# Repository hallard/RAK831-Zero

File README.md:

# Raspberry PI Zero RAK831 Lora Gateway Shield

This shield has been created to help wiring between Raspberry PI Zero and [RAK831][10] LoraWan concentrator Gateway and to be able to put the whole thing into a enclosure..

Then I decided to add some funky stuff like:

## Features (tested, working fine)

**Major updates in V1.5a**

 - Added connector to put a [Tiny GPS][46] breakout board 
 - Added switch/jumpers to select PI Serial to be connected to FTDI connector or from GPS RX/TX
 - Added footprint for RTC components or [Adafruit Breakout][47] (when used in local LoRaWAN server without Internet connexion)
 - Added a LED on ~~GPIO4~~ GPIO26 to light when GW is off so we can remove power safely (or whatever purpose)
 - Connected GPS PPS signal on GPIO4 and added a LED on this signal
 - **due to space constraints because of new features, some options to put PTH components have been removed**

**Minor tweaks in V1.4**

 - Labeling error on top silk for Murata OKI-78SR-5 (VIN VOUT were revesed) but correct on bottom silk
 - Added solder bat to be able to reverse 3V3/GND and/or SCL/SDA on I2C-1 connector 
 - Moved FTDI connector to lower position
 - Added I2C connector SILK number to identify them better
 - Added a LED on GPIO4 to light when GW is off so we can remove power safely

**Minor tweaks in V1.3b**

 - Reversed side of Murata OKI-78SR-5 to let some place for big OLED
 - Changed solder pad default power to use DC/DC 
 - Inversed the 2 OLED connectors to better seeing of RAK LED
 - Adjusted opening to see RAK LED to a better position

**Since V1.3**

 - Push button on GPIO17 to be able to shutdown PI Locally
 - Added FTDI connector to be able to take hand on PI console when in enclosure (lost network or whatever, no more need to get all off the enclosure and connect HDMI cable to see what's going on)
 - Added footprint for excellent Murata OKI-78SR-5 DC/DC 5V
 - Footprint for [RAK831][10] LoraWan concentrator (main goal)
 - I2C connectors to be able to add internal/external sensors or OLED such as BME280, SI7021, HTU21D SSD1306
 - Power with terminal block
 - 2 visual WS2812B Leds
 - Easy to build and solder, 0805 or PTH components
 - Holes to fix board on enclosure or other support
 - quick fix connector, you can plug/unplug PI Zero without soldering

Tiny GPS breakout board, buy [there][46]   

Tiny Adafruit RTC board, buy [there][47]    

## Detailed Description

No specific documentation for now, it's just a kind of wiring helper, please see Gateway section on [TTN Learn](https://www.thethingsnetwork.org/docs/gateways/) and also on [TTN Forums](https://www.thethingsnetwork.org/forum/t/the-hard-rak831-cafe-part-2/10576/) for more information on these gateways.

### Power

You can power the board with 5V going to Raspberry PI USB power directly or connecting 5V to the terminal blocks named VIN/GND, in this case use a descent 5V power supply. 

You can also use a Murata DC/DC Step down (see BOM), in this case you can power the board from DC 7V to 36V, this is what I do each time. ~~To use this feature you need to cut the trace on bottom side of PCB that connect VIN to 5V (vout)~~.

**Since V1.3b+ the trace is not connected anymore**. This means that Vin and Vout are not connected anymore. So if you don't use DC/DC and powering with 5V, you need to put some solder on the pad to connect vout to vin (5V).

### Pushbutton

The push button is connected between 3V3 and GPIO17. GPIO17 has a 10K pull down to ground so when pressed GPIO17 become High. The button can be soldered on board, or connected to the Terminal Blocks if you want to put an external one if you have the board in a closed enclosure for example.

Push button management is done my the monitoring service installed by the setup below

### LEDs

Led management is done my the monitoring service installed by the setup below

## Software Installation

Please follow the installation documented on the dedicated [repository][5] to install all needed and functionnal software:

- Initial configuration
- Multi Protocol Packet Forwarder
- Monitoring service (Led and Push Button)

## Schematics

## Boards 

### PCB 

**Top side**

**Bottom side**

### Assembled PCB (V1.3)

**Top side**

**Bottom side**

You can order the PCB of this board at PCBs.io 

- [V1.3][3] (obsolete)
- [V1.3b][4] (obsolete)
- [V1.4][6] 
- [V1.5a][8] Lastest one

Please not that there is special PCB version (not released yet) that fit in an indoor enclosure like the ones you can find on ebay. Search on ebay for `100x68x50mm IP66 Waterproof` or `100x68x50mm IP66 Waterproof clear` to find them.
- [V1.3][7] For outdoor enclosure (smaller PCB)

PCBs.io give me some reward when you order my designed boards from their site. This is pretty good, because I can use these rewards to create and design new boards and order boards for a discounted price, so if you don't care about PCB manufacturer please use PCBs.io.

## Assembled boards into nice enclosure 

With the samtec connector you can put the PI Zero on top or bottom, depending on your choice, just solder the sametec connector to the PCB side you need. You can also avoid connector soldering the PI directly on the board.

And here it is near to [The things node](https://www.thethingsnetwork.org/docs/devices/node/).

## Video of all

Click on image to see the video

## Bill Of Material

Nothing fancy, all components are 0805 and/or PTH and can be ordered almost anywhere (digikey, mouser, radiospare, ...). 
use only what you need dependings on what you want to do. You can find lot of components on ebay or aliexpress, but since vendors are often ephemere, I put for reference the BOM on well known providers.

Here is the [octopart BOM](https://octopart.com/bom-tool/bSeZiAE7)

If you have good reference for standoff like [this][44], just let me know.

## License

This work is licensed under a [Creative Commons Attribution-NonCommercial 4.0 International License](http://creativecommons.org/licenses/by-nc/4.0/)    
If you want to do commercial stuff with this project, please contact [CH2i company](https://www.ch2i.eu/en#support) so we can organize an simple agreement.

# Misc

See news and other projects on my [blog][1] 
 
[1]: https://hallard.me
[3]: https://PCBs.io/share/rpqDd
[4]: https://PCBs.io/share/z722g
[6]: https://PCBs.io/share/4qKoO
[7]: https://PCBs.io/share/zvYLj
[8]: https://www.pcbs.io/share/rwjd1

[5]: https://github.com/ch2i/LoraGW-Setup
[10]: http://www.rakwireless.com/en/WisKeyOSH/RAK831
[44]: https://www.ebay.com/itm/162036913864?var=461005633671
[45]: http://www2.mouser.com/ProductDetail/Murata-Power-Solutions/OKI-78SR-5-15-W36H-C/?qs=sGAEpiMZZMt6Q9lZSPl3Rb6uckMsyldgZf%2f4GdkUxM8%3d
[46]: http://www.electrodragon.com/product/gnss-module-atgm336h/
[47]: https://www.adafruit.com/product/3295

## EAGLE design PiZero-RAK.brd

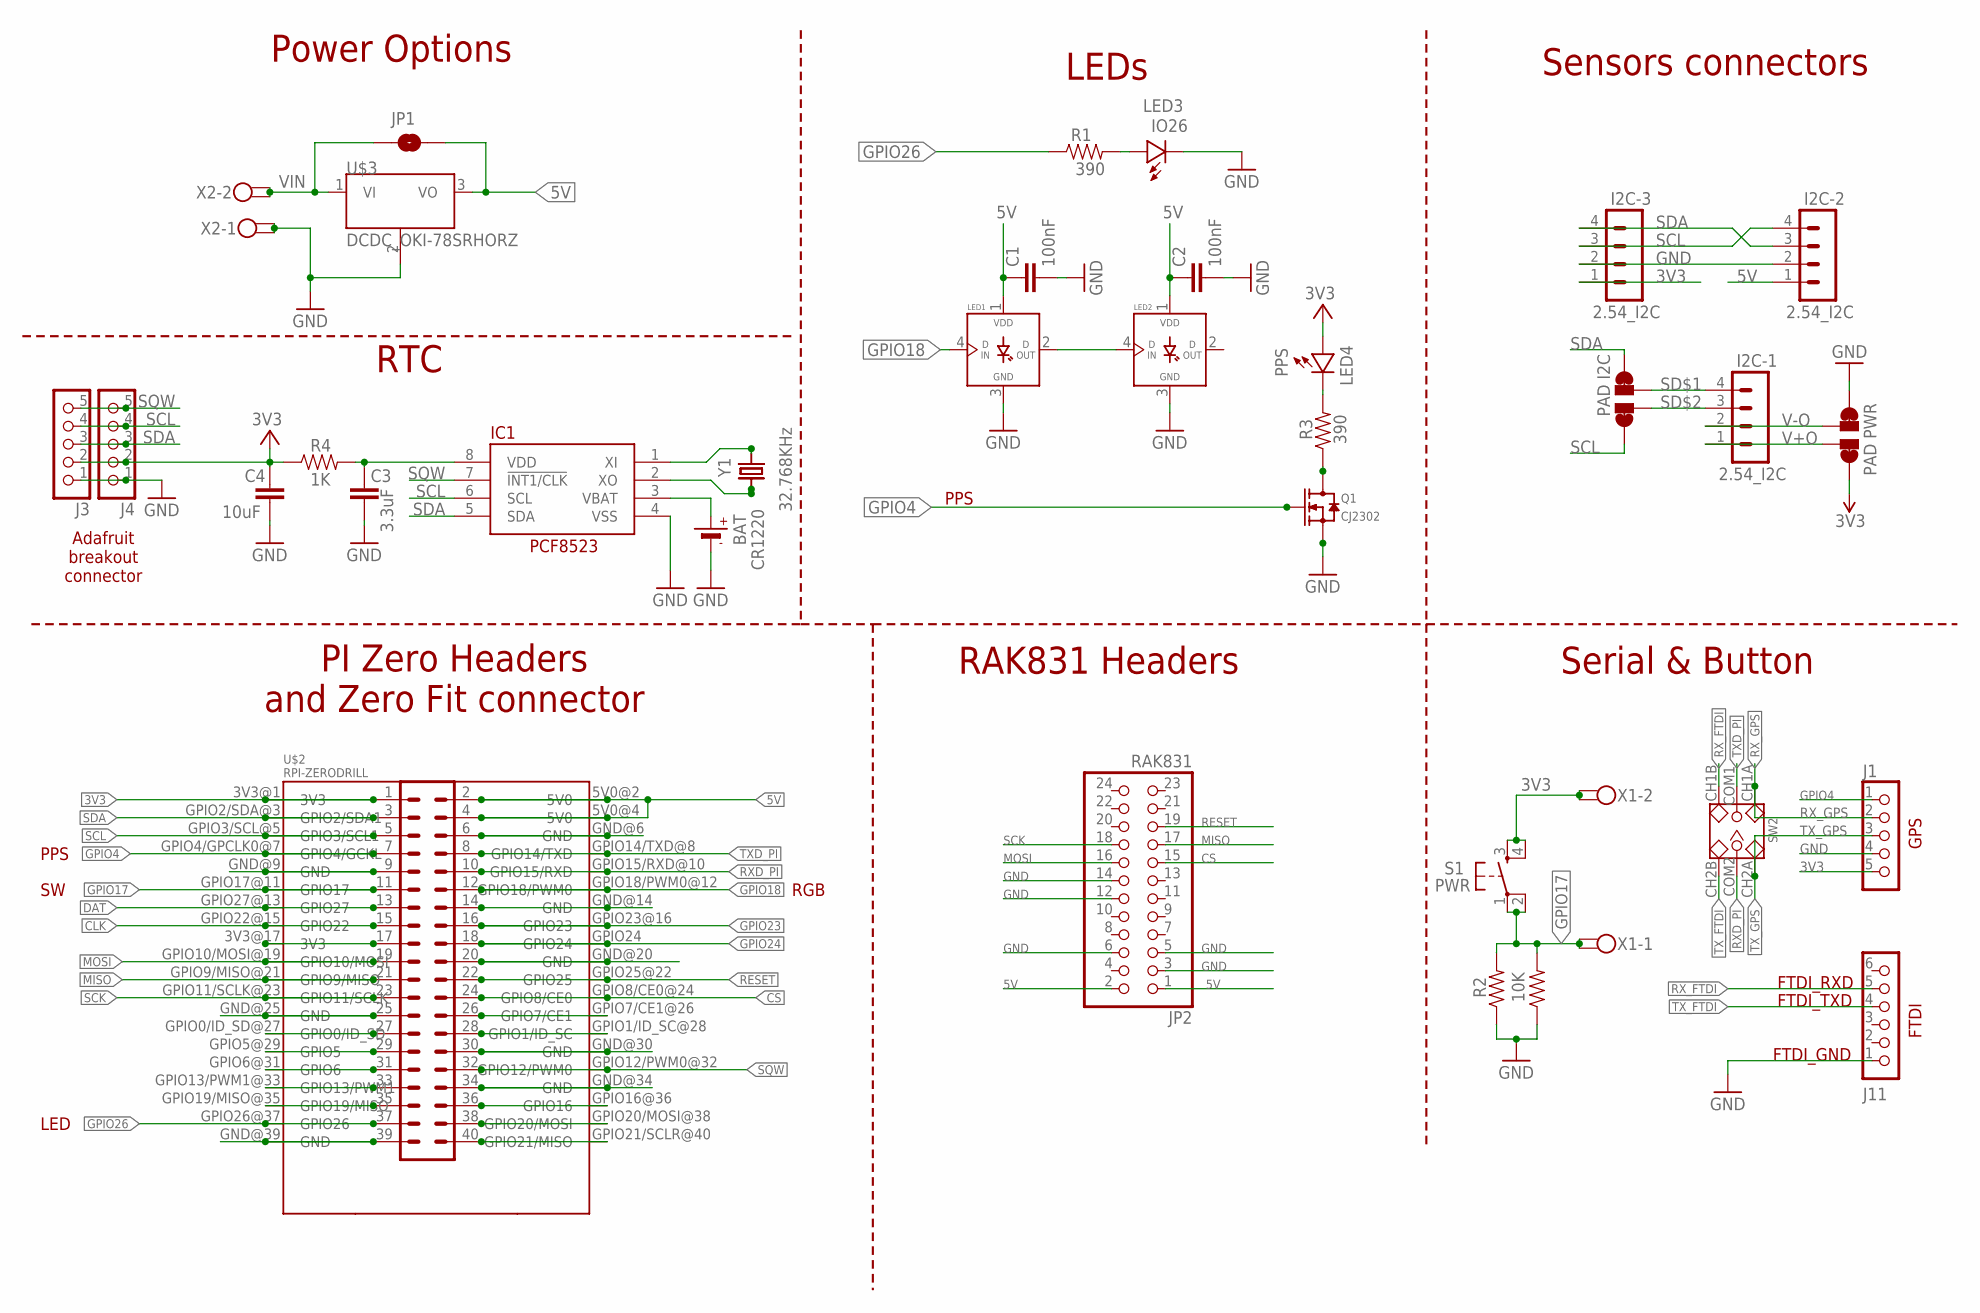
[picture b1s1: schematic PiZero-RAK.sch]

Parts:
BAT: CR1220
C1, C2: 100nF; 0805-CAP-LARGEPADS
C3: 3.3uF; 0805-CAP-LARGEPADS
C4: 10uF; 0805-CAP-LARGEPADS
I2C-1, I2C-2, I2C-3: 2.54_I2C; 1X04_NO_LOCK
IC1: PCF8523; SOIC8_150MIL
J1, J3, J4: CON_HEADER_1X05-PTH; M1X5
J2: CONN_20X2HLE; 2X20-HLE
J11: CON_HEADER_1X06-PTH; M1X6
JP1: JUMPER-PAD-2-NOYES_SILK; PAD-JUMPER-2-NO_YES_SILK
JP2: RAK831; 2X12
LED1, LED2: WS2812BLONG; WS2812B-LONG
LED3: IO26; 0805-LED-LARGEPADS
LED4: PPS; 0805-LED-LARGEPADS
Q1: CJ2302; SOT-23
R1, R3: 390; 0805-RES
R2: 10K; AXIAL-0.4
R4: 1K; 0805-RES
R105: RESISTOR0805-RES; 0805-RES
S1: PWR; TAC-SWITCH-PTH
SW2: DIP-TOGGLE-SWITCH-2CH-(2X3P-2.54); SW6-2.54-9.0X3.5X3.2+2.0MM
U$2: RPI-ZERODRILL; RPI-ZERO-DRILLS
U$3: DCDC_OKI-78SRHORZ; OKI-78SRH
U$4: PAD PWR; PAD-JUMPER-SWAP
U$5: PAD I2C; PAD-JUMPER-SWAP
X1: SPTAF_23.5; FFKV2_35
X2: SPTAF_25.0MM; SPTAF_2X50
Y1: 32.768KHz; TC26H
Y2: CRYSTAL8X3.8SMT; CRYSTAL_8X3.8

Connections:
3V3: C4.1, I2C-3.1, J1.5, J2.1, J3.2, J4.2, LED4.PLUS, R4.1, S1.3, S1.4, U$2.3V3@1 (3V3), U$4.4, U$4.44 (4), X1.2 (1), X1.2A (2)
3V3@17: J2.17, U$2.3V3@17 (3V3)
5V: C1.1, C2.1, I2C-2.1, J2.2, J2.4, JP1.2, JP2.1, JP2.2, LED1.1 (VDD), LED2.1 (VDD), U$2.5V0@2 (5V0), U$2.5V0@4 (5V0), U$3.3 (VO)
CLK: J2.15, U$2.GPIO22@15 (GPIO22)
CS: J2.24, JP2.15, U$2.GPIO8/CE0@24 (GPIO8/CE0)
DAT: J2.13, U$2.GPIO27@13 (GPIO27)
GND: BAT.-, C1.2, C2.2, C3.2, C4.2, I2C-2.2, I2C-3.2, IC1.4 (VSS), J1.4, J2.6, J2.9, J2.14, J2.20, J2.25, J2.30, J2.34, J2.39, J3.1, J4.1, J11.1, JP2.3, JP2.5, JP2.6, JP2.12, JP2.14, LED1.3 (GND), LED2.3 (GND), LED3.MINUS, Q1.2 (S), R2.P$1 (1), R105.1, U$2.GND@6 (GND), U$2.GND@9 (GND), U$2.GND@14 (GND), U$2.GND@20 (GND), U$2.GND@25 (GND), U$2.GND@30 (GND), U$2.GND@34 (GND), U$2.GND@39 (GND), U$3.2 (GND), U$4.1, U$4.11 (1), X2.1, X2.1A (2)
GPIO4: J1.1, J2.7, Q1.1 (G), U$2.GPIO4/GPCLK0@7 (GPIO4/GCKL)
GPIO17: J2.11, R2.P$2 (2), R105.2, S1.1, S1.2, U$2.GPIO17@11 (GPIO17), X1.1, X1.1A (2)
GPIO18: J2.12, LED1.4 (DIN), U$2.GPIO18/PWM0@12 (GPIO18/PWM0)
GPIO19: J2.35, U$2.GPIO19/MISO@35 (GPIO19/MISO)
GPIO23: J2.16, U$2.GPIO23@16 (GPIO23)
GPIO24: J2.18, U$2.GPIO24
GPIO26: J2.37, R1.1, U$2.GPIO26@37 (GPIO26)
MISO: J2.21, JP2.17, U$2.GPIO9/MISO@21 (GPIO9/MISO)
MOSI: J2.19, JP2.16, U$2.GPIO10/MOSI@19 (GPIO10/MOSI)
unnamed: J2.26, U$2.GPIO7/CE1@26 (GPIO7/CE1)
unnamed: LED3.PLUS, R1.2
unnamed: IC1.1 (XI), Y1.1, Y2.P$4 (2)
unnamed: Q1.3 (D), R3.1
unnamed: J2.28, U$2.GPIO1/ID_SC@28 (GPIO1/ID_SC)
unnamed: J2.36, U$2.GPIO16@36 (GPIO16)
unnamed: J2.38, U$2.GPIO20/MOSI@38 (GPIO20/MOSI)
unnamed: J2.40, U$2.GPIO21/SCLR@40 (GPIO21/MISO)
unnamed: J2.27, U$2.GPIO0/ID_SD@27 (GPIO0/ID_SD)
unnamed: J2.29, U$2.GPIO5@29 (GPIO5)
unnamed: J2.31, U$2.GPIO6@31 (GPIO6)
unnamed: J2.33, U$2.GPIO13/PWM1@33 (GPIO13/PWM1)
unnamed: LED4.MINUS, R3.2
unnamed: IC1.2 (XO), Y1.2, Y2.P$1 (1)
unnamed: LED1.2 (DOUT), LED2.4 (DIN)
RESET: J2.22, JP2.19, U$2.GPIO25@22 (GPIO25)
RXD_PI: J2.10, SW2.COM2, U$2.GPIO15/RXD@10 (GPIO15/RXD)
RX_FTDI: J11.5, SW2.CH1B
RX_GPS: J1.2, SW2.CH1A
SCK: J2.23, JP2.18, U$2.GPIO11/SCLK@23 (GPIO11/SCLK)
SCL: I2C-2.4, I2C-3.3, IC1.6 (SCL), J2.5, J3.4, J4.4, U$2.GPIO3/SCL@5 (GPIO3/SCL1), U$5.1, U$5.11 (1)
SD$1: I2C-1.4, U$5.3
SD$2: I2C-1.3, U$5.2
SDA: I2C-2.3, I2C-3.4, IC1.5 (SDA), J2.3, J3.3, J4.3, U$2.GPIO2/SDA@3 (GPIO2/SDA1), U$5.4, U$5.44 (4)
SQW: IC1.7 (!INT1/CLK), J2.32, J3.5, J4.5, U$2.GPIO12/PWM0@32 (GPIO12/PWM0)
TXD_PI: J2.8, SW2.COM1, U$2.GPIO14/TXD@8 (GPIO14/TXD)
TX_FTDI: J11.4, SW2.CH2B
TX_GPS: J1.3, SW2.CH2A
V+O: I2C-1.1, U$4.3
V-O: I2C-1.2, U$4.2
VBAT: BAT.+$1 (+), IC1.3 (VBAT)
VDD: C3.1, IC1.8 (VDD), R4.2
VIN: JP1.1, U$3.1 (VI), X2.2 (1), X2.2A (2)

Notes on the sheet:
RAK831 Headers
Power Options
Serial & Button
LEDs
Sensors connectors
PI Zero Headers and Zero Fit connector
FTDI_RXD
FTDI_TXD
FTDI_GND
GPS
FTDI
PPS
RGB
LED
RTC
Adafruit breakout connector

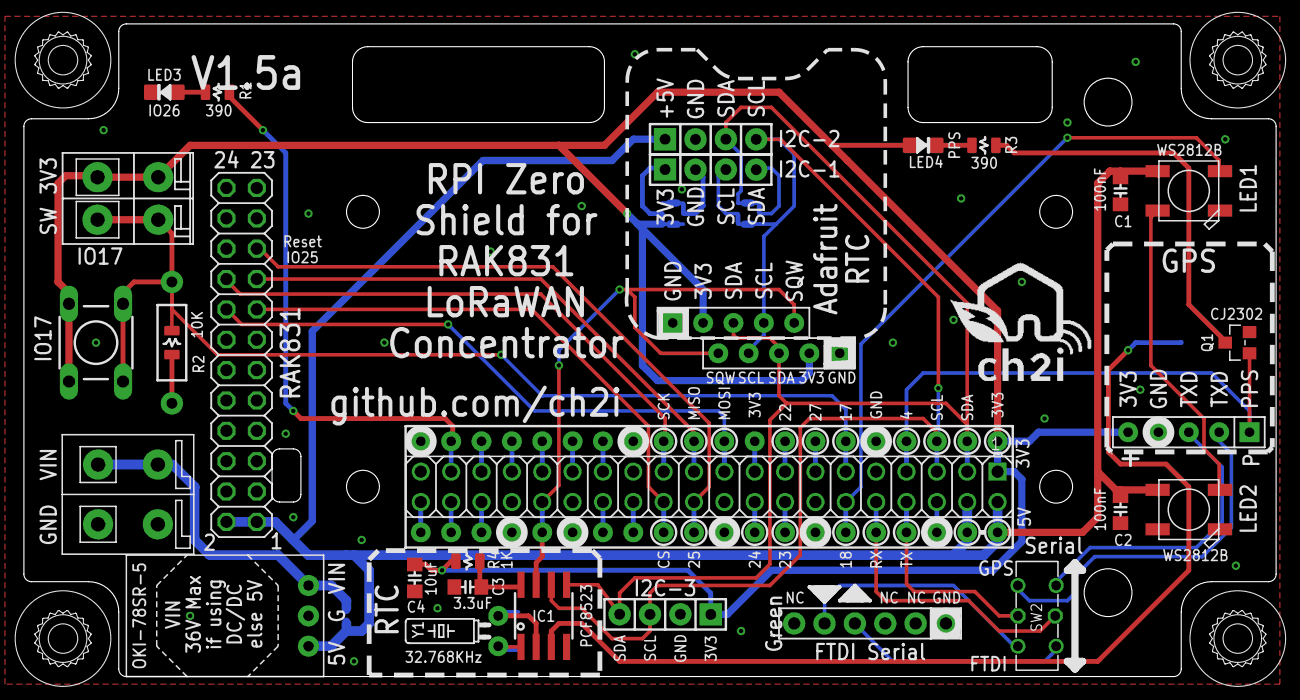
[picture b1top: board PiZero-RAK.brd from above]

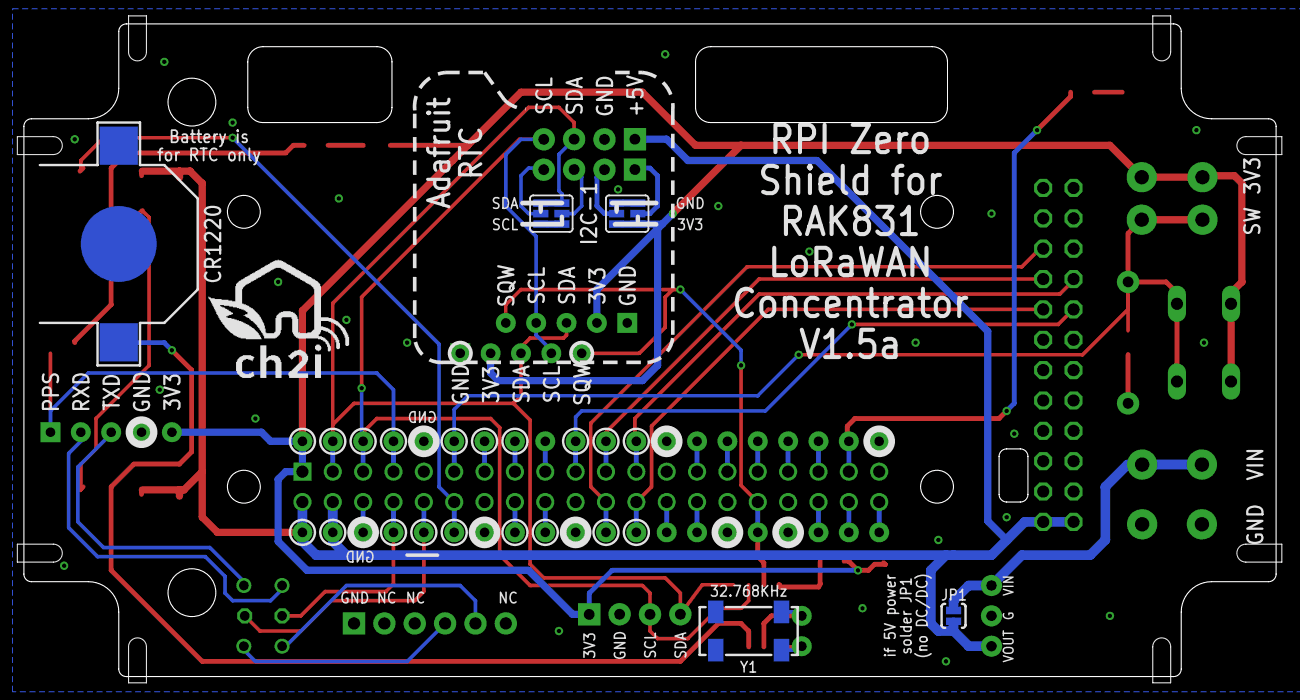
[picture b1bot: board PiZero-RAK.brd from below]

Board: 2 copper layers, 104.8 x 54.6 mm, 39 parts (6 on the bottom side), 49 nets.

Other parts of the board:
U$1, U$9: LOGO_CH2I_110MM
U$10: ENCLOSURE_1591B

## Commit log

2018-01-21 :circus_tent: Added .gitattributes
2018-01-21 Creation
2018-01-21 Added connector info
2018-01-21 Links error
2018-01-21 Corrected links
2018-01-21 Added the things node
2018-01-21 Cosmetic updates
2018-01-22 added doc
2018-01-22 cosmetic
2018-02-05 Bump to V1.3b
2018-02-05 Typo
2018-02-05 Added V1.3b PCBs.io link
2018-03-22 Added video link
2018-03-22 Video text
2018-03-23 Added V1.4 links and doc
2018-03-23 V1.4
2018-03-23 Bump to V1.4
2018-03-23 Added link to outdoor PCB version
2018-06-08 V1.5
2018-06-08 Bump to V1.5
2018-06-08 Renamed pictures
2018-06-08 Fixed pictures links
2018-06-09 Bump to V1.5a
2018-06-22 Fixed BOM link

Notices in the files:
parts and their libraries:
GeekAmmo: Licensing:Creative Commons ShareAlike 4.0 International - https://creativecommons.org/licenses/by-sa/4.0
microbuilder: This work is placed in the public domain, and may be freely used for commercial and non-commercial work with the following conditions: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
